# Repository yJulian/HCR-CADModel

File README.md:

From
https://github.com/open-dynamic-robot-initiative/master-board

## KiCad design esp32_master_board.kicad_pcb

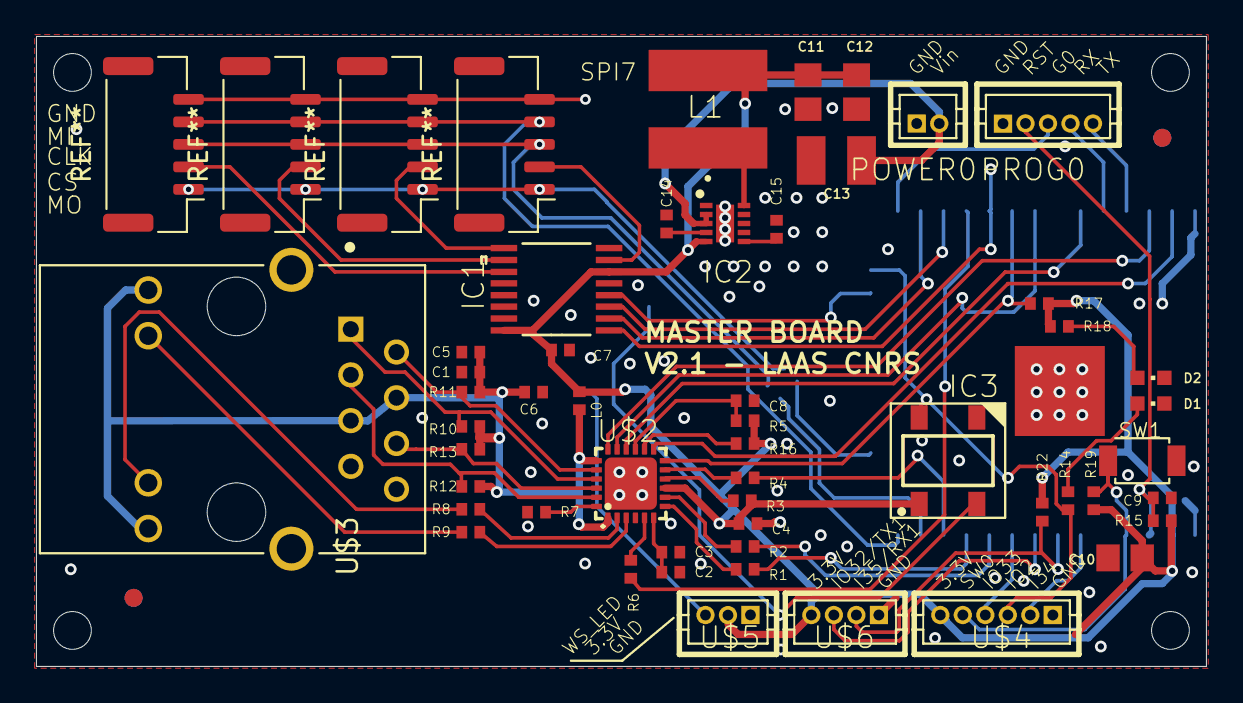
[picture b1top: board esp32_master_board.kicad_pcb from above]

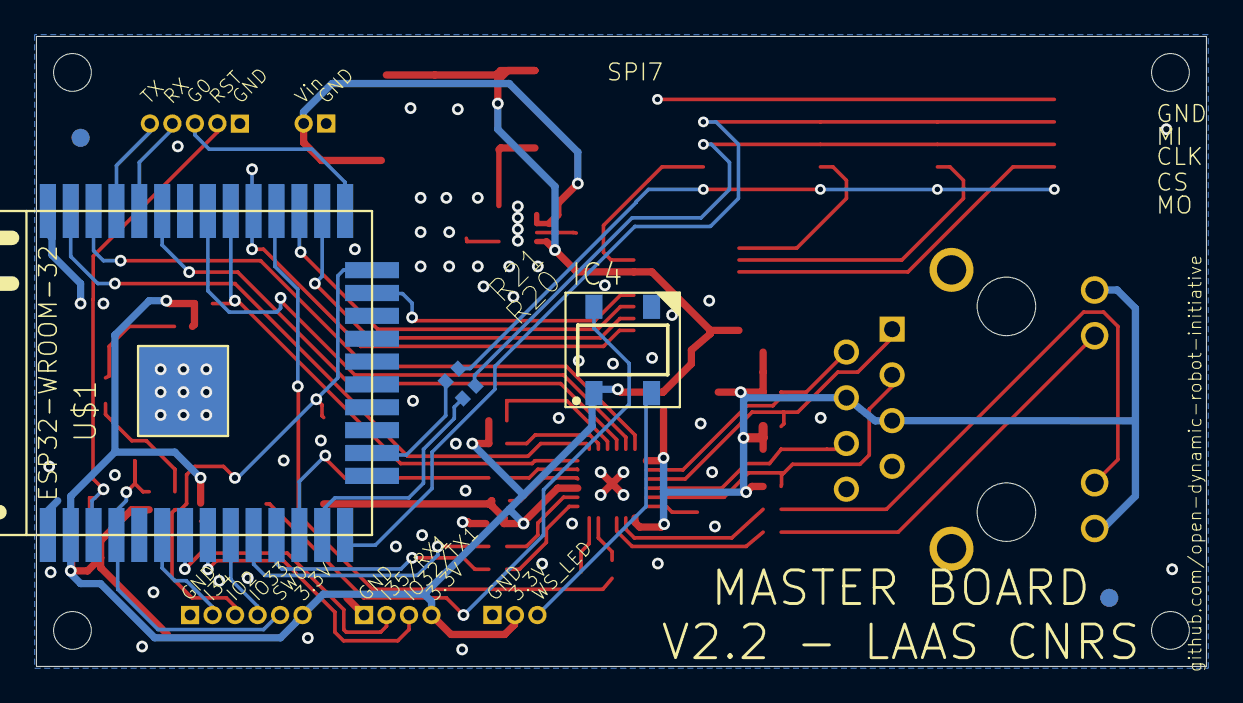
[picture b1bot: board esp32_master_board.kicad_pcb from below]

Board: 2 copper layers, 65.0 x 35.0 mm, 62 parts (6 on the bottom side), 53 nets.

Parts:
C1: 22n; 0402
C2: 470p; 0402
C3: 1u LOW ESR; 0402
C4, C5, C6, C7, C8, C9: 100n; 0402
C10, C11, C12: 22u; C0805_334
C13: 2.2u; C1210
C14: 1u; 0402
C15: 3.3n; 0402
D1: RED; CHIPLED_0603_259
D2: GREEN; CHIPLED_0603_259
IC1: SN74HC138PW; SOP65P640X120-16N
IC2: MAX17502EATB+T; SON50P200X300X80-11N
IC3, IC4: WS2812B
L0: 0; 0402
L1: 15uH; LPS6235
POWER0: DF13-2P-1.25DSA
PROG0: DF13-5P-1.25DSA
R1, R2, R3, R4, R20, R21: 10; 0402
R5, R15, R16, R19, R22: 4.7k; 0402
R6: 33; 0402
R7: 12.1k; 0402
R8, R9, R14, R18: 330; 0402
R10, R11, R12, R13: 49.9; 0402
R17: 1.5k; 0402
REF1, REF2, REF3, REF4: VISION_REF10
SW1: B3U-1000P-2P-SMD; SW2-2.6-3.0X2.5X1.2+0.4MM_8004989
U$1: ESP32-WROOM
U$2: LAN8720; QFN24
U$3: HR911105A; HANRUN_HR911105A
U$4: DF13-6P-1.25DSA
U$5: DF13-3P-1.25DSA
U$6: DF13-4P-1.25DSA
UNK_HOLE_0: dummyfp0
UNK_HOLE_1: dummyfp1
UNK_HOLE_2: dummyfp2
UNK_HOLE_3: dummyfp3

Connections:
BOOT_MODE: PROG0.P$3, U$1.IO0
CLK50: R6.1, U$1.IO17
CRS: R4.1, U$1.IO27
CS_A0: IC1.1, U$1.IO5
CS_A1: IC1.2, U$1.IO4
CS_A2: IC1.3, U$1.IO16
GND: C1.2, C2.2, C3.2, C4.2, C5.2, C6.2, C7.2, C8.2, C9.2, C10.2, C11.2, C12.2, C13.2, C14.1, C15.2, D1.C, D2.C, IC1.5, IC1.8, IC2.1, IC2.9, IC2.11, IC3.3, IC4.3, POWER0.P$1, PROG0.P$1, R7.1, SW1.1, U$1.GND1, U$1.GND2, U$1.GND3, U$1.GND4, U$1.GND5, U$2.EXP, U$3.8, U$3.15, U$3.16, U$4.P$1, U$5.P$1, U$6.P$1
I34: U$1.IO34, U$4.P$2
I35_RX1: R22.2, U$1.IO35, U$6.P$2
IO2: IC3.4, R14.2, U$1.IO2, U$4.P$3
IO32_TX1: U$1.IO32, U$6.P$3
IO33: U$1.IO33, U$4.P$4
LED1: R9.2, U$2.3
LED2: R8.2, U$2.2
MDC: U$1.IO23, U$2.13
MDIO: R17.1, U$1.IO18, U$2.12
unnamed: R1.2, U$2.7
unnamed: R2.2, U$2.8
unnamed: R3.2, U$2.10
unnamed: R4.2, U$2.11
unnamed: R6.2, U$2.5
unnamed: R7.2, U$2.24
unnamed: R10.1, U$2.21, U$3.1
unnamed: R11.1, U$2.20, U$3.2
unnamed: R12.1, U$2.23, U$3.3
unnamed: R13.1, U$2.22, U$3.6
unnamed: R8.1, U$3.11
unnamed: R9.1, U$3.10
unnamed: R16.1, U$2.14
unnamed: C2.1, C3.1, U$2.6
unnamed: C14.2, IC2.4
unnamed: D1.A, R14.1
unnamed: R21.2, U$1.IO13
unnamed: IC2.10, L1.1
unnamed: IC3.2, IC4.4
unnamed: D2.A, R18.2
unnamed: R20.2, U$1.IO14
unnamed: C15.1, IC2.6
unnamed: C13.1, IC2.2, IC2.3, POWER0.P$2
NRST: C8.1, R5.1, U$2.15
RST: C9.1, PROG0.P$2, R15.1, U$1.EN
RX: PROG0.P$4, U$1.RX
RXD0: R2.1, U$1.IO25
RXD1: R1.1, U$1.IO26
SPI_CS: IC1.4, U$1.IO15
SW0: R19.1, SW1.2, U$1.SENSOR_VP, U$4.P$5
TX: PROG0.P$5, U$1.TX
TXD0: U$1.IO19, U$2.17
TXD1: U$1.IO22, U$2.18
TX_EN: U$1.IO21, U$2.16
VCC: C4.1, C7.1, C10.1, C11.1, C12.1, IC1.6, IC1.16, IC2.5, IC3.1, IC4.1, L0.1, L1.2, R3.1, R5.2, R15.2, R16.2, R17.2, R18.1, R19.2, R22.1, U$1.3V3, U$2.9, U$4.P$6, U$5.P$2, U$6.P$4
VDD: C1.1, C5.1, C6.1, L0.2, R10.2, R11.2, R12.2, R13.2, U$2.1, U$2.19, U$3.4, U$3.5, U$3.9, U$3.12
WSLED_OUT: IC4.2, U$5.P$3

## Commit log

2025-05-27 Initial
2025-07-24 Fusion Model
